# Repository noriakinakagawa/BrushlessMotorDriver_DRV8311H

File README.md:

# BrushlessMotorDriver_DRV8311H
DRV8311Hを使ったブラシレスモータドライバ評価基板version 0.1

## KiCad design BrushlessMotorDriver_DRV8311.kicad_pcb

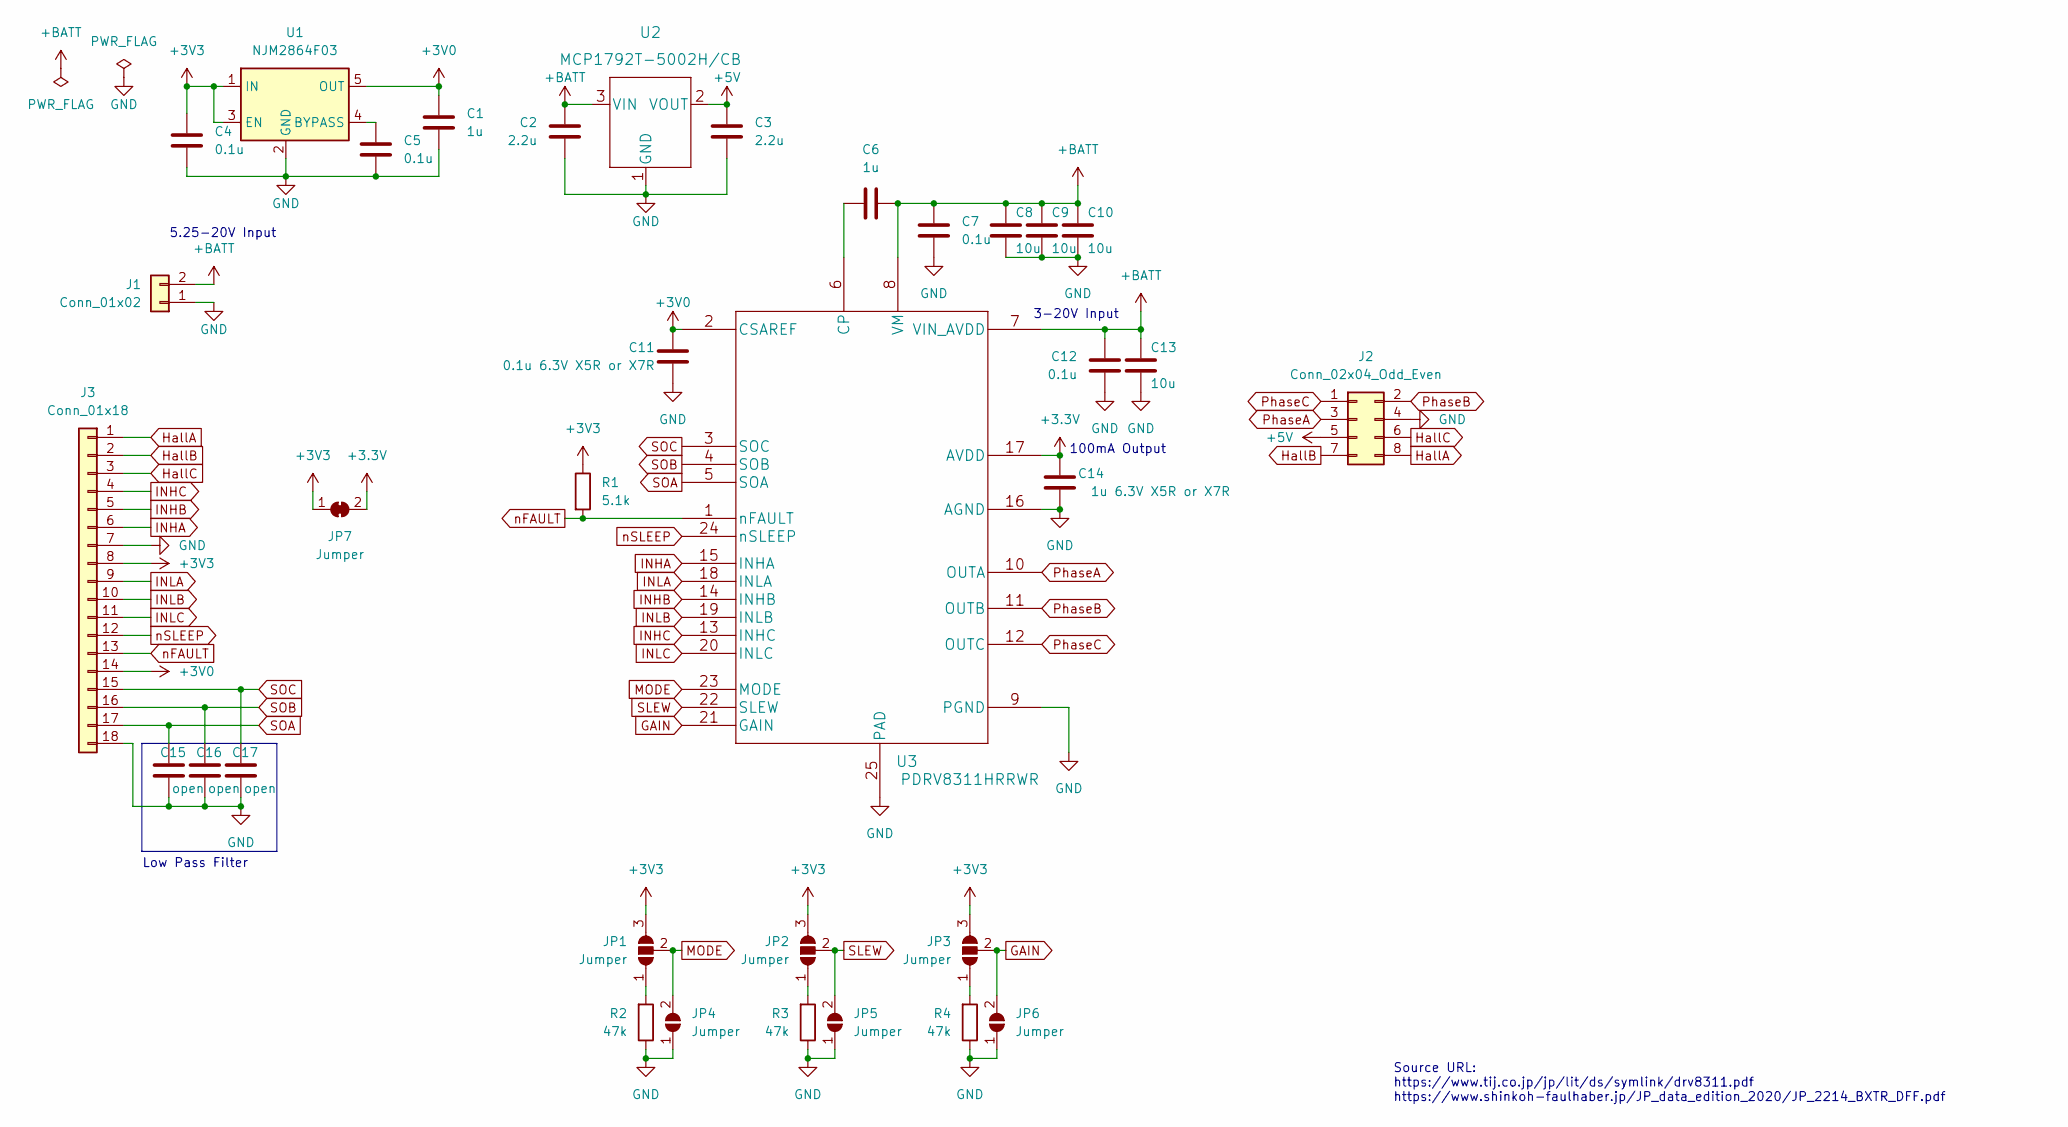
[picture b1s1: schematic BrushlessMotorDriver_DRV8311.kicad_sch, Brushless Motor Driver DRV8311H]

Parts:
C1, C6: 1u; C_0603_1608Metric
C2, C3: 2.2u; C_0603_1608Metric
C4, C5, C7, C12: 0.1u; C_0603_1608Metric
C8, C9, C10, C13: 10u; C_0603_1608Metric
C11: 0.1u 6.3V X5R or X7R; C_0603_1608Metric
C14: 1u 6.3V X5R or X7R; C_0603_1608Metric
C15, C16, C17: open; C_0603_1608Metric
J1: Conn_01x02; PinHeader_1x02_P2.54mm_Vertical
J2: Conn_02x04_Odd_Even; PinHeader_2x04_P2.54mm_Vertical
J3: Conn_01x18; PinHeader_1x18_P2.54mm_Vertical
JP1, JP2, JP3: Jumper; SolderJumper-3_P1.3mm_Open_RoundedPad1.0x1.5mm_NumberLabels
JP4, JP5, JP6: Jumper; SolderJumper-2_P1.3mm_Open_RoundedPad1.0x1.5mm
JP7: Jumper; SolderJumper-2_P1.3mm_Bridged_RoundedPad1.0x1.5mm
R1: 5.1k; R_0603_1608Metric
R2, R3, R4: 47k; R_0603_1608Metric
U1: NJM2864F03; TSOT-23-5
U2: MCP1792T-5002H/CB; MCP1792T-5002H&slash_CB
U3: PDRV8311HRRWR

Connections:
+3V0: C1.2, C11.2, J3.14, U1.5 (OUT), U3.2 (CSAREF)
+5V: C3.2, J2.5, U2.2 (VOUT)
+BATT: C2.2, C6.2, C7.2, C8.2, C9.2, C10.2, C12.2, C13.2, J1.2, U2.3 (VIN), U3.7 (VIN_AVDD), U3.8 (VM)
GAIN: JP3.2 (C), JP6.2 (B), U3.21 (GAIN)
GND: C1.1, C2.1, C3.1, C4.1, C5.1, C7.1, C8.1, C9.1, C10.1, C11.1, C12.1, C13.1, C14.1, C15.1, C16.1, C17.1, J1.1, J2.4, J3.7, J3.18, JP4.1 (A), JP5.1 (A), JP6.1 (A), R2.1, R3.1, R4.1, U1.2 (GND), U2.1 (GND), U3.9 (PGND), U3.16 (AGND), U3.25 (PAD)
HallA: J2.8, J3.1
HallB: J2.7, J3.2
HallC: J2.6, J3.3
INHA: J3.6, U3.15 (INHA)
INHB: J3.5, U3.14 (INHB)
INHC: J3.4, U3.13 (INHC)
INLA: J3.9, U3.18 (INLA)
INLB: J3.10, U3.19 (INLB)
INLC: J3.11, U3.20 (INLC)
MODE: JP1.2 (C), JP4.2 (B), U3.23 (MODE)
unnamed: C5.2, U1.4 (BYPASS)
unnamed: C6.1, U3.6 (CP)
unnamed: JP1.1 (A), R2.2
unnamed: JP2.1 (A), R3.2
unnamed: JP3.1 (A), R4.2
PhaseA: J2.3, U3.10 (OUTA)
PhaseB: J2.2, U3.11 (OUTB)
PhaseC: J2.1, U3.12 (OUTC)
SLEW: JP2.2 (C), JP5.2 (B), U3.22 (SLEW)
SOA: C15.2, J3.17, U3.5 (SOA)
SOB: C16.2, J3.16, U3.4 (SOB)
SOC: C17.2, J3.15, U3.3 (SOC)
nFAULT: J3.13, R1.2, U3.1 (nFAULT)
nSLEEP: J3.12, U3.24 (nSLEEP)

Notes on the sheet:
3-20V Input
Low Pass Filter
100mA Output
Source URL: https://www.tij.co.jp/jp/lit/ds/symlink/drv8311.pdf https://www.shinkoh-faulhaber.jp/JP_data_edition_2020/JP_2214_BXTR_DFF.pdf
5.25-20V Input

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
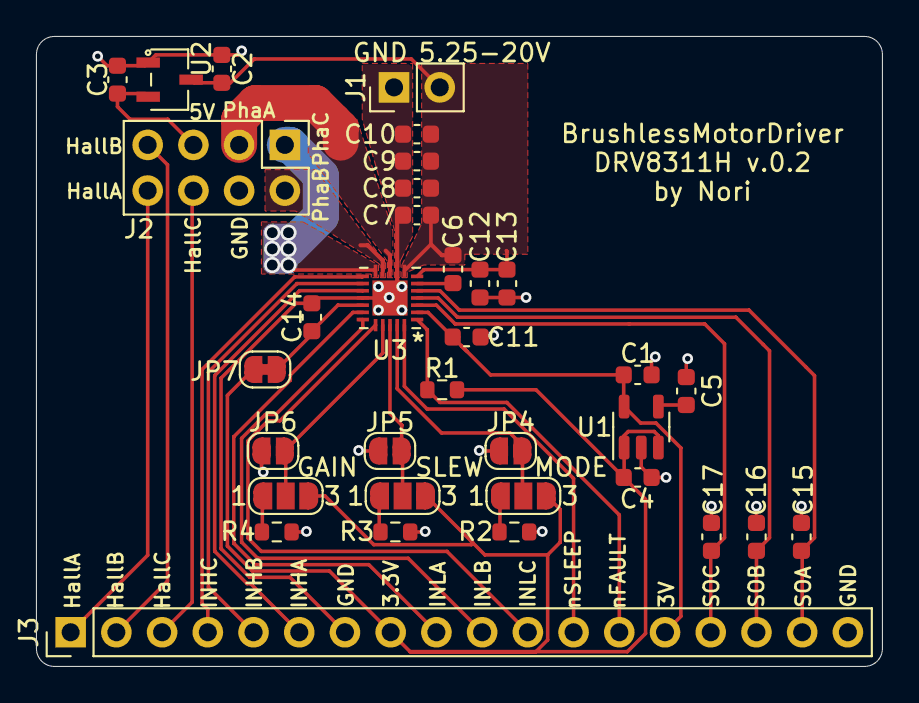
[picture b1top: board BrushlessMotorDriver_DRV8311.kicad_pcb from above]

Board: 2 copper layers, 47.0 x 35.0 mm, 34 parts (0 on the bottom side), 30 nets.
